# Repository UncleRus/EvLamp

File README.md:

# EvLamp

Clean implementation of Alex Guyver's FireLamp analogue in pure C for ESP32.

## What it does

Display beautiful effects on a multiple matrices of NxN WS2812B/SK6812/APA106/SM16703 LEDs.

### Features

- ~30 very beautiful effects from different authors, each with set of parameters
- WiFi connectivity in station or access point modes (support for DHCP/static IP addressing)
- [JSON HTTP API for remote controlling](API.md)
- Embedded webserver for remote controlling from browser
- *TODO: OTA*

## Hardware

You will need:

- ESP32 or ESP32-S3 (ESP32-S2/ESP32-C3/ESP32-C4 and others are not supported)
- One or more WS2812B/SK6812/APA106/SM16703 LED matrices
- 4 buttons:
    - Main: long press - On/Off, click - next effect
    - Up/Down: brightness up/down
    - Reset: long press - Reset settings to defaults

You can use the KiCad 7 project located in the [hardware directory](hardware) and containing
an example implementation: a schematic, a simple board and ready-made Gerber files for production
(compatible with JLCPCB requirements).

### LED matrix

The LEDs in the matrix are connected in series like a snake, starting from the bottom row:

The sizes of the most common matrices:
- 8x8
- 32x8
- 16x16

You can build your own matrix with widely available WS2812B/SK6812/APA106 LED strips.

The dimensions of the matrix side are limited to the range 8..128 and
number of pixels in matrix cannot be more than 1024.

I do not recommend using matrices with a large number of LEDs due to the maximum frame
rate limitations: for a matrix containing 512 LEDs, this limit is 60 fps, and for a matrix of
1024 LEDs maximal fps is 30. It is better to use multiple small matrices.

### Single matrix configuration

To control one matrix, only one GPIO pin of the microcontroller is needed:

This configuration is the simplest supported.

### Multiple LED matrices (blocks) configuration

You can connect up to 8 LED matrices of the same size to different GPIO pins and achieve high resolution
rendering of the effect. For example:

### Minimal recommended configuration

1 block, 16x16 LEDs, 90 fps max.

### Maximal recommended configuration

2x4 blocks, each 32x16 LEDs.
Total screen dimensions: 64x64, 4096 LEDs, 60 fps max.

### Changing LED layout

Configure your LED layout at runtime by API or in browser ("Menu -> LEDs Settings"):

## Changing default settings 

You can select GPIOs, set default WiFi config, LED layout and more in `idf.py menuconfig`
(`*** EvLamp configuration ***`). 

## How to build firmware

- Setup latest ESP-IDF master
- `git clone https://github.com/UncleRus/EvLamp.git`
- `git submodule init --recursive --remote`
- `idf.py menuconfig`
- `idf.py build`
- `idf.py erase-flash` (not necessary but recommended)
- `idf.py flash` to upload firmware to ESP

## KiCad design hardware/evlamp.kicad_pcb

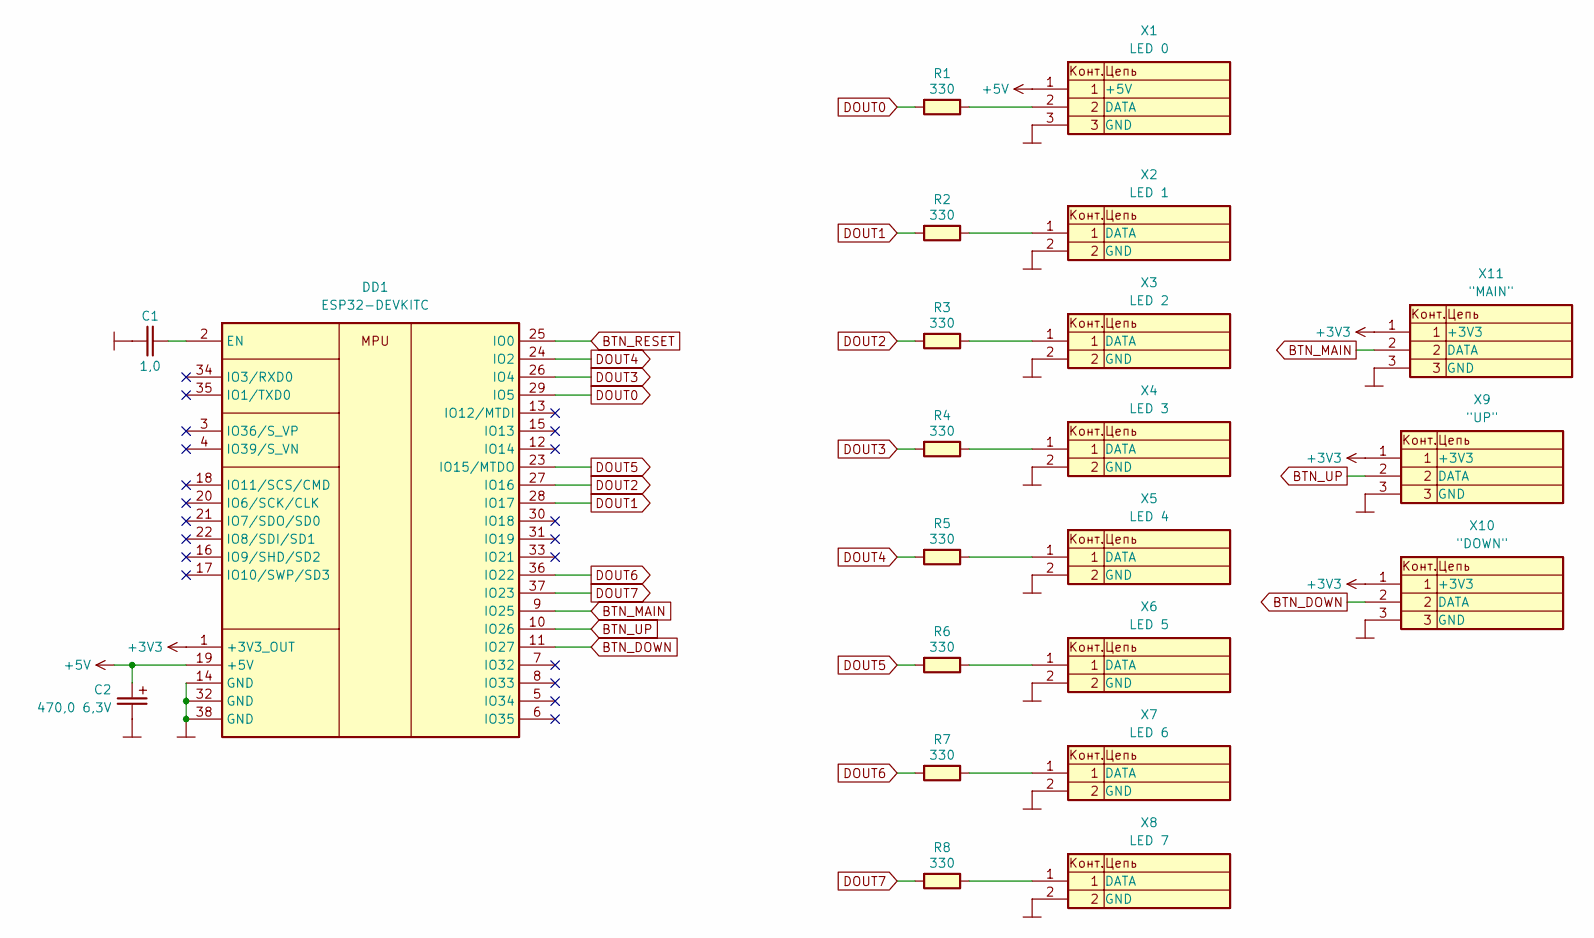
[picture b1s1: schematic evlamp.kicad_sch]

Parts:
C1: 1,0; C_0805_2012Metric_Pad1.18x1.45mm_HandSolder
C2: 470,0 6,3V; CP_EIA-7343-31_Kemet-D_Pad2.25x2.55mm_HandSolder
DD1: ESP32-DEVKITC
R1, R2, R3, R4, R5, R6, R7, R8: 330; R_0805_2012Metric_Pad1.20x1.40mm_HandSolder
X1: LED 0; TerminalBlock_bornier-3_P5.08mm
X2: LED 1; TerminalBlock_bornier-2_P5.08mm
X3: LED 2; TerminalBlock_bornier-2_P5.08mm
X4: LED 3; TerminalBlock_bornier-2_P5.08mm
X5: LED 4; TerminalBlock_bornier-2_P5.08mm
X6: LED 5; TerminalBlock_bornier-2_P5.08mm
X7: LED 6; TerminalBlock_bornier-2_P5.08mm
X8: LED 7; TerminalBlock_bornier-2_P5.08mm
X9: "UP"; PinHeader_1x03_P2.54mm_Vertical
X10: "DOWN"; PinHeader_1x03_P2.54mm_Vertical
X11: "MAIN"; PinHeader_1x03_P2.54mm_Vertical

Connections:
+3V3: DD1.1 (+3V3_OUT), X9.1, X10.1, X11.1
+5V: C2.1, DD1.19 (+5V), X1.1
BTN_DOWN: DD1.11 (IO27), X10.2
BTN_MAIN: DD1.9 (IO25), X11.2
BTN_RESET: DD1.25 (IO0)
BTN_UP: DD1.10 (IO26), X9.2
DOUT0: DD1.29 (IO5), R1.1 (L)
DOUT1: DD1.28 (IO17), R2.1 (L)
DOUT2: DD1.27 (IO16), R3.1 (L)
DOUT3: DD1.26 (IO4), R4.1 (L)
DOUT4: DD1.24 (IO2), R5.1 (L)
DOUT5: DD1.23 (IO15/MTDO), R6.1 (L)
DOUT6: DD1.36 (IO22), R7.1 (L)
DOUT7: DD1.37 (IO23), R8.1 (L)
GND: C1.1, C2.2, DD1.14 (GND), DD1.32 (GND), DD1.38 (GND), X1.3, X2.2, X3.2, X4.2, X5.2, X6.2, X7.2, X8.2, X9.3, X10.3, X11.3
unnamed: C1.2, DD1.2 (EN)
unnamed: R1.2 (R), X1.2
unnamed: R2.2 (R), X2.1
unnamed: R3.2 (R), X3.1
unnamed: R4.2 (R), X4.1
unnamed: R5.2 (R), X5.1
unnamed: R6.2 (R), X6.1
unnamed: R7.2 (R), X7.1
unnamed: R8.2 (R), X8.1

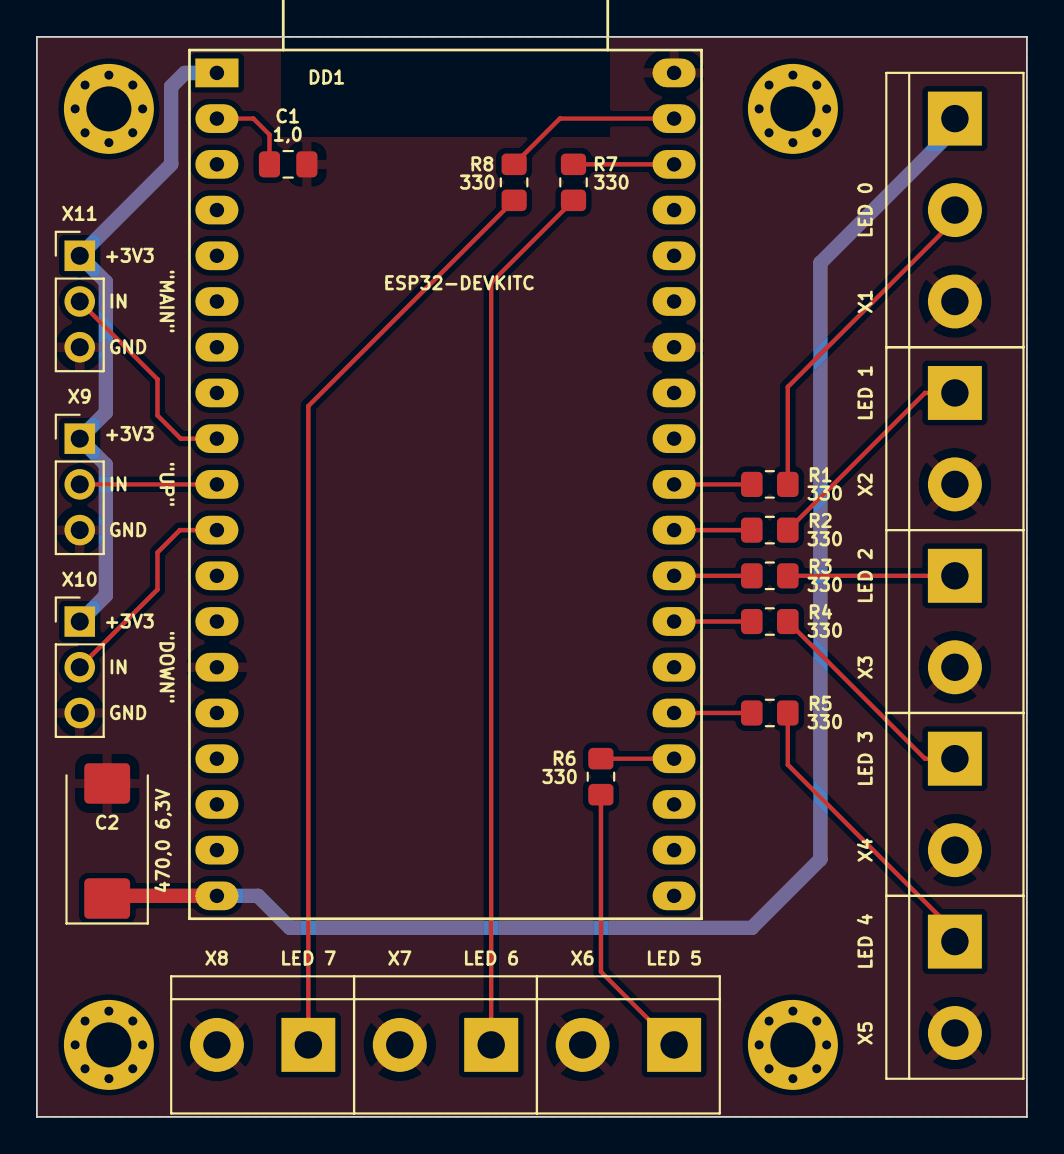
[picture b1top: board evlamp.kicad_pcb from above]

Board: 2 copper layers, 55.0 x 60.0 mm, 22 parts (0 on the bottom side), 23 nets.

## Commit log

2021-04-27 First prototype
2021-04-27 update esp-idf-lib
2021-04-30 first working version
2021-04-30 change default effect params, add button support
2021-04-30 update esp-idf-lib, disable button temporaly
2021-04-30 input poll moved from timer to separate task
2021-04-30 fixed CMakeLists.txt, add on/off func
2021-04-30 add metaballs effect
2021-05-01 fix default effect params, move rendering to app core
2021-05-01 add water effect, update esp-idf-lib for workarond Wifi/RMT bug
2021-05-01 add dns to wifi, return back rendering to fbanimation
2021-05-01 add holiday lights effect
2021-05-01 add new effect hoop
2021-05-02 update esp-idf-lib, fix WiFi/RMT bug, port libnsgif, add SPIFFS and gifs
2021-05-03 fix metaballs palette, fix typos, lower log verbosity, fix surface init
2021-05-03 remove spiffs image, update esp-idf-lib
2021-05-03 short palette in fire effect, change lamp effect params from hsv to rgb
2021-05-04 add mustach, add sys_settings to JSON
2021-05-04 template engine proto
2021-05-05 fix dns logging, set fallback dns in STA mode
2021-05-07 web templates support, started API
2021-05-07 fix api
2021-05-07 api: add /api/lamp/state POST handler
2021-05-07 api: add methods to get/set effect params
2021-05-07 api: add POST /api/settings/leds
2021-05-07 api: add POST /api/settings/wifi, wifi: fix AP channel
2021-05-07 api: fix sta and ap password, rm templates, embed jquery & css
2021-05-07 fix GET/POST /api/lamp/effect
2021-05-08 flash: OTA partition table, app szie = 0x150000
2021-05-08 web: embed jquery-ui
2021-05-09 remove libnsgif, remove led_gpio from settings
2021-05-10 added new buttons, throw out fb_animation, cleanup in surface code
2021-05-10 update button defaults
2021-05-10 Add reset button
2021-05-10 api: reset vol_settings
2021-05-11 twister effect, update esp-idf-lib
2021-05-11 fix typo
2021-05-11 fix twister effect
2021-05-13 web: saving wifi & leds settings, reset, reboot
2021-05-19 web: update interface to more suitable for mobile devices
2021-05-19 web: fix style of messages
2021-05-19 new effect 'Flower'
2021-05-19 new effect 'Polar lights'
2021-05-20 add effect displaying embedded gifs
2021-05-21 fix wifi output, fix rainbow params
2021-05-21 fix README
2021-05-21 fix surface_prepare_effect(), fix lava params
2021-05-21 fix lava effect
2021-05-21 added relax effect
2021-05-21 fix relax effect
2021-05-22 fix surface_set_effect
2021-05-22 add log output to surface_pause()
2021-05-22 new lava mode
2021-05-22 fix bugs in effects
2021-05-22 new effect 'rollrays'
2021-05-22 fix movement in rollrays
2021-05-24 rename 'rollrays' to 'radiant wheel'
2021-05-24 fix build, web: add 'reset effect settings' menu, update icons
2021-05-24 web: fix return to main after declining reset
2021-05-24 web: more responsive sliders, surface: log on brightness and fps change
2021-05-25 web: fix checkbox in wifi settings form
2021-06-02 wifi: fix static IP in AP mode
2021-06-02 main: fix button event handler
2021-06-02 wifi: fix set DNS in AP mode
2021-06-05 OTA skel
2021-06-06 ota: bugfix, change api response
2021-07-09 ota 2
2021-07-09 add separate reset button level, update defaults, update esp-idf-lib
2021-08-12 better wifi logging
2021-08-12 rename EPARAM to PARAM_VAL
2021-10-01 new effect "Peacock tale"
2021-12-30 fix errors, add first gh ota try
2022-03-25 update es-idf-lib
2022-04-30 ota: merge master, update cert
2022-04-30 new effect, fix clnag tidy warnings
2022-05-01 add more palettes to 'fire' effect, new effect 'diagonal movements', fix 'colors' effect
2022-05-01 new effect 'diagonal movements'
2022-05-02 new effect whirls, add global palettes and use it in lava and fire effects
2022-05-02 add possibility of horizontal and vertical matrix mirroring
2022-05-02 new effect "sun"
2022-05-02 new effects 'Spaceships' and 'Fireflies'
2022-05-02 Add schematics
2022-05-03 add API description
2022-05-03 fix API.md formatting
2022-05-05 cpu speed set to 240MHz, small fixes
2022-05-05 new params in 'crazybees' effect, small fixes
2022-05-05 update libnsgif, update 'gif' effect
2022-05-09 small fixes
2022-05-24 initial multichannel support
2022-05-25 add hw layouts to readme, fix surface init bug, fix 'gif', fix 'hoop'
2022-05-25 Update API description
2022-05-25 fix README.md
2022-05-25 fix 'rays' effect
2022-05-26 fix readme, add params to 'wheel' and 'twister'
2022-05-26 add 'tunnel' effect
2022-05-26 add 'dunes' effect
2022-05-26 Fix bug in brightness restriction calculation
2022-05-26 move height adjustment in 'polar lights' to parameters
2022-05-26 workaround ESP-IDF bug with stopping HTTP server on WiFi disconnect
2022-05-26 a little bit friendly web control page
2022-05-27 Update esp-idf-lib, support for SM16703
2022-05-27 set random seed on init
2022-05-28 fix default GOIOs for matrices
2022-05-28 add KiCad project and Gerber files
2022-05-29 update KiCad project
2022-05-29 s/RMT_CHANNEL_MAX/MAX_SURFACE_BLOCKS/
2022-05-29 fix check of led type in api, suppress deprecated rmt warning, first try of surface rotation
2022-06-18 add checkbox support to effect parameters
2022-06-18 remove old surface rotation
2022-07-10 fix wifi sta password bug
2022-07-10 up version, small fixes
2022-08-08 update to latest esp-idf, esp-idf-lib
2022-12-19 update libs
2022-12-19 fix ip-data saving bug in api, update esp-idf-lib
2023-06-06 feat: add 'octopus' effect, update esp-idf-lib
2023-08-03 feat: new effects "octopus" and "nuclear noise"
2023-08-03 fix: fixed finite gif animation
2023-11-28 remove 'colors' effect, begin matrix rotation, add target check
